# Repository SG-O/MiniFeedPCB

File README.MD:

# Main PCB for automated SMT Feeder #

## Documentation ##

You can find the manufacturing documentation [here.](https://github.com/SG-O/MiniFeedPCB/tree/master/Doc)

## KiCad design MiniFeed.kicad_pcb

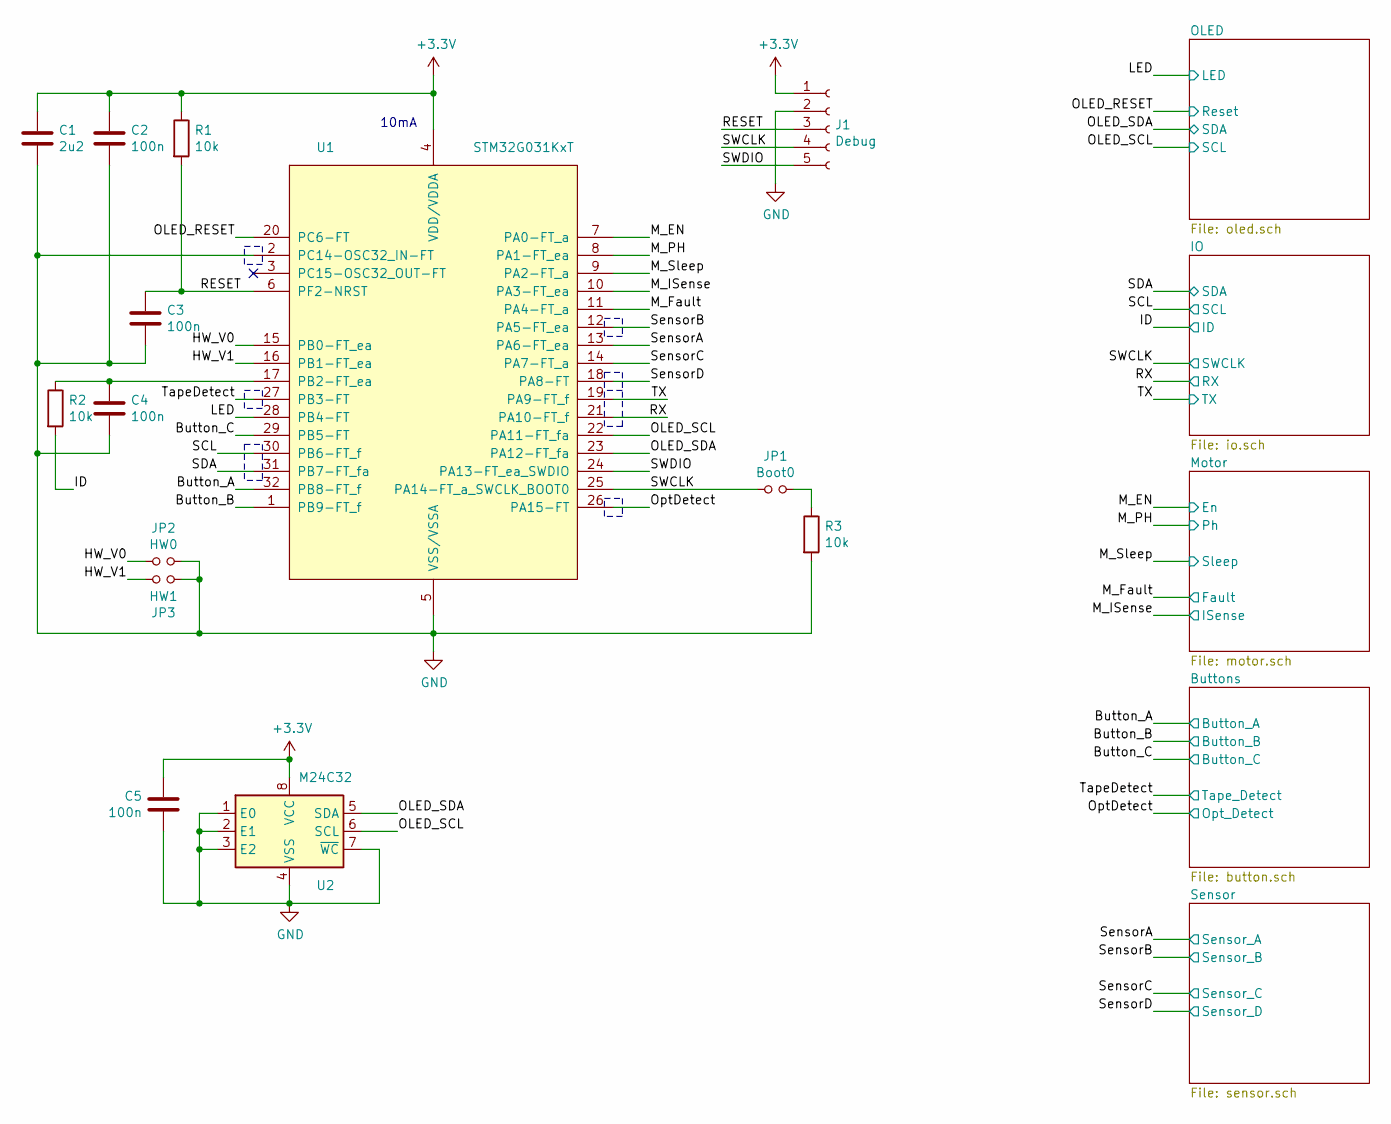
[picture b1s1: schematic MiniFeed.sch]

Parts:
C1: 2u2; C_0805_2012Metric; lcsc# C19110
C2, C3, C4, C5: 100n; C_0603_1608Metric; lcsc# C1591
J1: Debug; PinSocket_1x05_P1.27mm_Vertical
JP1: Boot0; SolderJumper-2_P1.3mm_Open_RoundedPad1.0x1.5mm
JP2: HW0; SolderJumper-2_P1.3mm_Open_RoundedPad1.0x1.5mm
JP3: HW1; SolderJumper-2_P1.3mm_Open_RoundedPad1.0x1.5mm
R1, R2, R3: 10k; R_0603_1608Metric; lcsc# C128781
U1: STM32G031KxT; LQFP-32_7x7mm_P0.8mm; lcsc# C432203
U2: M24C32; SOIC-8_3.9x4.9mm_P1.27mm; lcsc# C7998

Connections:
+3V3: C1.1, C2.1, C5.1, J1.1, R1.1, U1.4 (VDD/VDDA), U2.8 (VCC); also elsewhere on the board
/Button_A: U1.32 (PB8-FT_f); also elsewhere on the board
/Button_B: U1.1 (PB9-FT_f); also elsewhere on the board
/Button_C: U1.29 (PB5-FT); also elsewhere on the board
/HW_V0: JP2.1, U1.15 (PB0-FT_ea)
/HW_V1: JP3.1, U1.16 (PB1-FT_ea)
/ID: R2.2; also elsewhere on the board
/LED: U1.28 (PB4-FT); also elsewhere on the board
/M_EN: U1.7 (PA0-FT_a); also elsewhere on the board
/M_Fault: U1.11 (PA4-FT_a); also elsewhere on the board
/M_ISense: U1.10 (PA3-FT_ea); also elsewhere on the board
/M_PH: U1.8 (PA1-FT_ea); also elsewhere on the board
/M_Sleep: U1.9 (PA2-FT_a); also elsewhere on the board
/OLED_RESET: U1.20 (PC6-FT); also elsewhere on the board
/OLED_SCL: U1.22 (PA11-FT_fa), U2.6 (SCL); also elsewhere on the board
/OLED_SDA: U1.23 (PA12-FT_fa), U2.5 (SDA); also elsewhere on the board
/OptDetect: U1.26 (PA15-FT); also elsewhere on the board
/RESET: C3.1, J1.3, R1.2, U1.6 (PF2-NRST)
/RX: U1.21 (PA10-FT_f); also elsewhere on the board
/SCL: U1.30 (PB6-FT_f); also elsewhere on the board
/SDA: U1.31 (PB7-FT_fa); also elsewhere on the board
/SWCLK: J1.4, JP1.1, U1.25 (PA14-FT_a_SWCLK_BOOT0); also elsewhere on the board
/SWDIO: J1.5, U1.24 (PA13-FT_ea_SWDIO)
/SensorA: U1.13 (PA6-FT_ea); also elsewhere on the board
/SensorB: U1.12 (PA5-FT_ea); also elsewhere on the board
/SensorC: U1.14 (PA7-FT_a); also elsewhere on the board
/SensorD: U1.18 (PA8-FT); also elsewhere on the board
/TX: U1.19 (PA9-FT_f); also elsewhere on the board
/TapeDetect: U1.27 (PB3-FT); also elsewhere on the board
GND: C1.2, C2.2, C3.2, C4.2, C5.2, J1.2, JP2.2, JP3.2, R3.2, U1.2 (PC14-OSC32_IN-FT), U1.5 (VSS/VSSA), U2.1 (E0), U2.2 (E1), U2.3 (E2), U2.4 (VSS), U2.7 (~WC); also elsewhere on the board
unnamed: C4.1, R2.1, U1.17 (PB2-FT_ea)
unnamed: JP1.2, R3.1

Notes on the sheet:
10mA

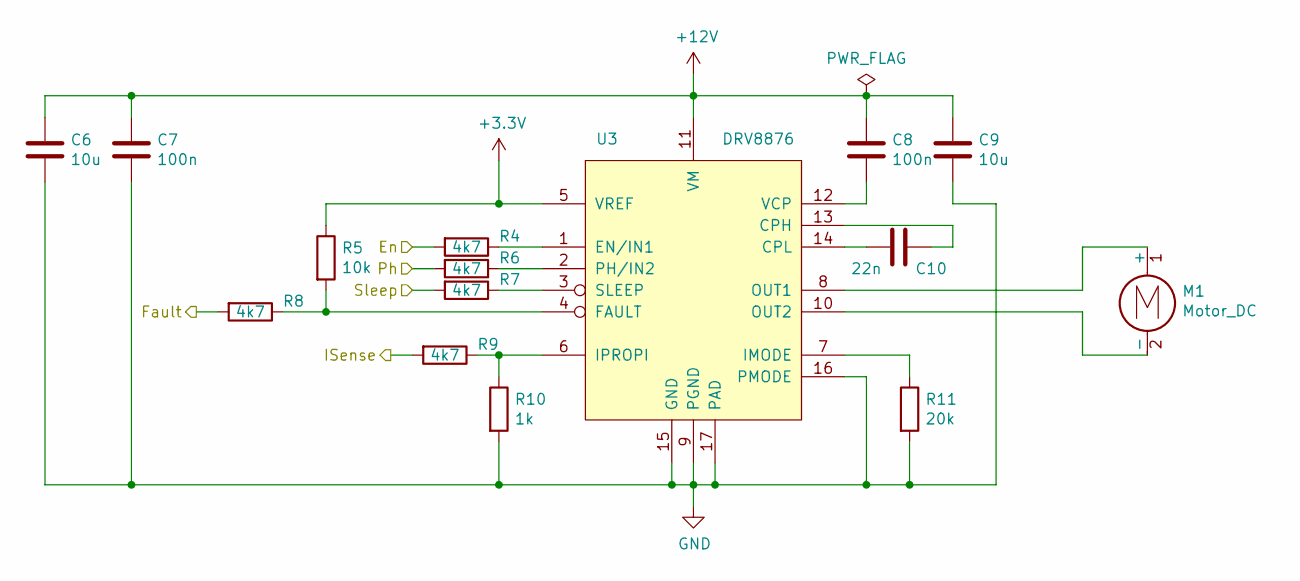
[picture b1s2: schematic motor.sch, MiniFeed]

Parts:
C6, C9: 10u; C_1206_3216Metric; lcsc# C14860
C7, C8: 100n; C_0603_1608Metric; lcsc# C1591
C10: 22n; C_0603_1608Metric; lcsc# C21122
M1: Motor_DC; MotorN20
R4, R6, R7, R8, R9: 4k7; R_0603_1608Metric; lcsc# C304093
R5: 10k; R_0603_1608Metric; lcsc# C128781
R10: 1k; R_0603_1608Metric; lcsc# C165976
R11: 20k; R_0603_1608Metric; lcsc# C135618
U3: DRV8876; HTSSOP-16-1EP_4.4x5mm_P0.65mm_EP3.4x5mm_Mask2.46x2.31mm_The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; lcsc# C575551

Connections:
+3V3: R5.1, U3.5 (VREF); also elsewhere on the board
+12V: C6.1, C7.1, C8.1, C9.1, U3.11 (VM); also elsewhere on the board
/M_EN: R4.2; also elsewhere on the board
/M_Fault: R8.2; also elsewhere on the board
/M_ISense: R9.2; also elsewhere on the board
/M_PH: R6.2; also elsewhere on the board
/M_Sleep: R7.2; also elsewhere on the board
GND: C6.2, C7.2, C9.2, R10.2, R11.2, U3.9 (PGND), U3.15 (GND), U3.16 (PMODE), U3.17 (PAD); also elsewhere on the board
unnamed: C8.2, U3.12 (VCP)
unnamed: C10.1, U3.13 (CPH)
unnamed: C10.2, U3.14 (CPL)
unnamed: M1.1 (+), U3.8 (OUT1)
unnamed: M1.2 (-), U3.10 (OUT2)
unnamed: R4.1, U3.1 (EN/IN1)
unnamed: R5.2, R8.1, U3.4 (FAULT)
unnamed: R6.1, U3.2 (PH/IN2)
unnamed: R7.1, U3.3 (SLEEP)
unnamed: R9.1, R10.1, U3.6 (IPROPI)
unnamed: R11.1, U3.7 (IMODE)

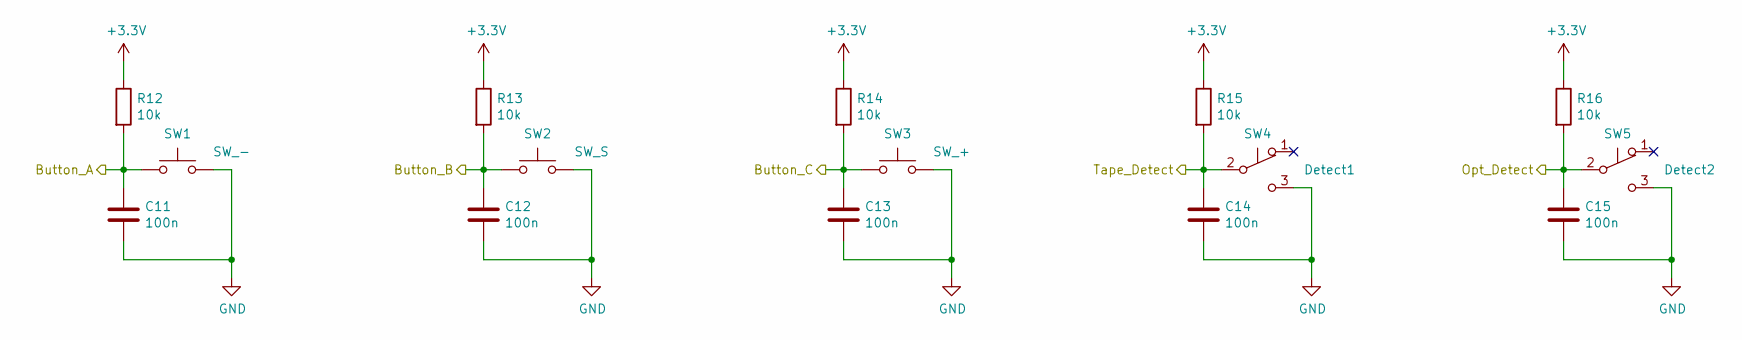
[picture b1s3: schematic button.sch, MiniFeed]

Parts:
C11, C12, C13, C14, C15: 100n; C_0603_1608Metric; lcsc# C1591
R12, R13, R14, R15, R16: 10k; R_0603_1608Metric; lcsc# C128781
SW1: SW_-; SW_SPST_TS-1065A-B3D4; lcsc# C498295
SW2: SW_S; SW_SPST_TS-1065A-B3D4; lcsc# C498295
SW3: SW_+; SW_SPST_TS-1065A-B3D4; lcsc# C498295
SW4: Detect1; MicroSwitchSMDLanding
SW5: Detect2; MicroSwitchSMDLanding

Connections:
+3V3: R12.1, R13.1, R14.1, R15.1, R16.1; also elsewhere on the board
/Button_A: C11.1, R12.2, SW1.1; also elsewhere on the board
/Button_B: C12.1, R13.2, SW2.1; also elsewhere on the board
/Button_C: C13.1, R14.2, SW3.1; also elsewhere on the board
/OptDetect: C15.1, R16.2, SW5.2 (B); also elsewhere on the board
/TapeDetect: C14.1, R15.2, SW4.2 (B); also elsewhere on the board
GND: C11.2, C12.2, C13.2, C14.2, C15.2, SW1.2, SW2.2, SW3.2, SW4.3 (C), SW5.3 (C); also elsewhere on the board

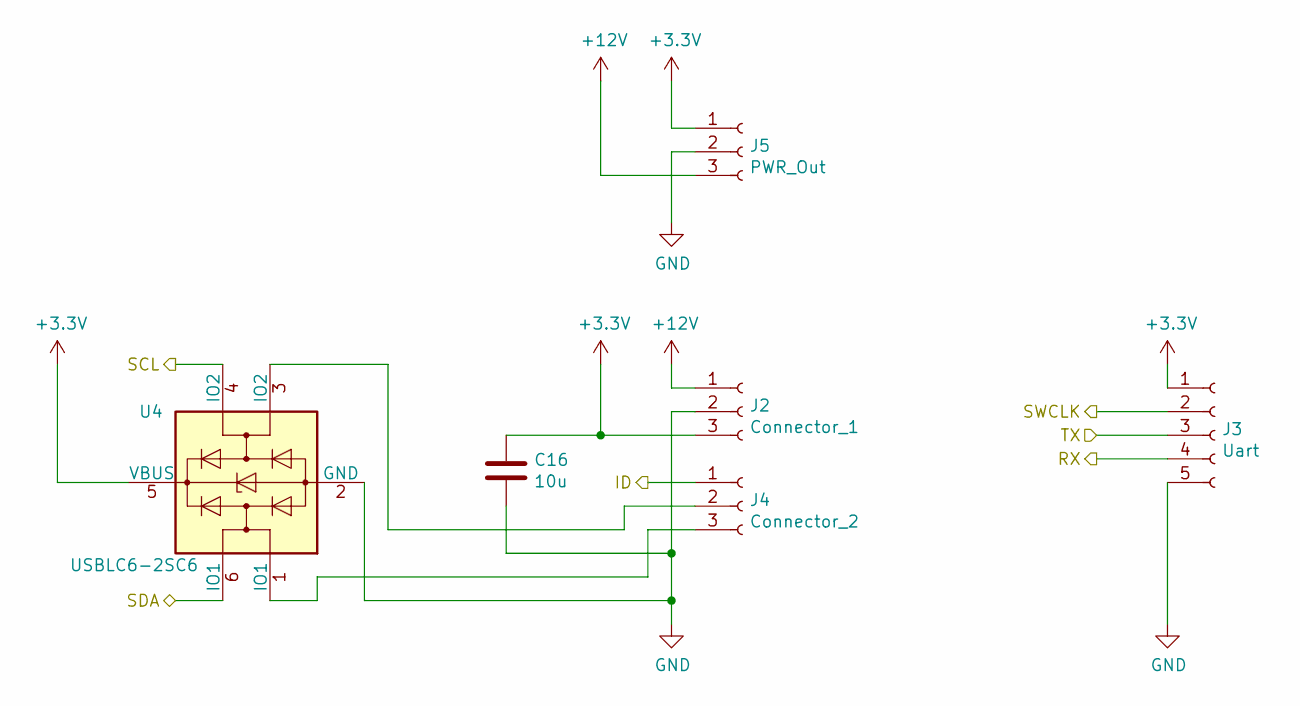
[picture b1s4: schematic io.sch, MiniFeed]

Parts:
C16: 10u; C_1206_3216Metric; lcsc# C14860
J2: Connector_1; PogoTarget_P2.5
J3: Uart; PinSocket_1x05_P2.54mm_Vertical
J4: Connector_2; PogoTarget_P2.5
J5: PWR_Out; PinSocket_1x03_P1.27mm_Vertical_SMD_Pin1Left
U4: USBLC6-2SC6; SOT-23-6; lcsc# C558442

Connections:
+3V3: C16.1, J2.3, J3.1, J5.1, U4.5 (VBUS); also elsewhere on the board
+12V: J2.1, J5.3; also elsewhere on the board
/ID: J4.1; also elsewhere on the board
/RX: J3.4; also elsewhere on the board
/SCL: U4.4 (IO2); also elsewhere on the board
/SDA: U4.6 (IO1); also elsewhere on the board
/SWCLK: J3.2; also elsewhere on the board
/TX: J3.3; also elsewhere on the board
GND: C16.2, J2.2, J3.5, J5.2, U4.2 (GND); also elsewhere on the board
unnamed: J4.2, U4.3 (IO2)
unnamed: J4.3, U4.1 (IO1)

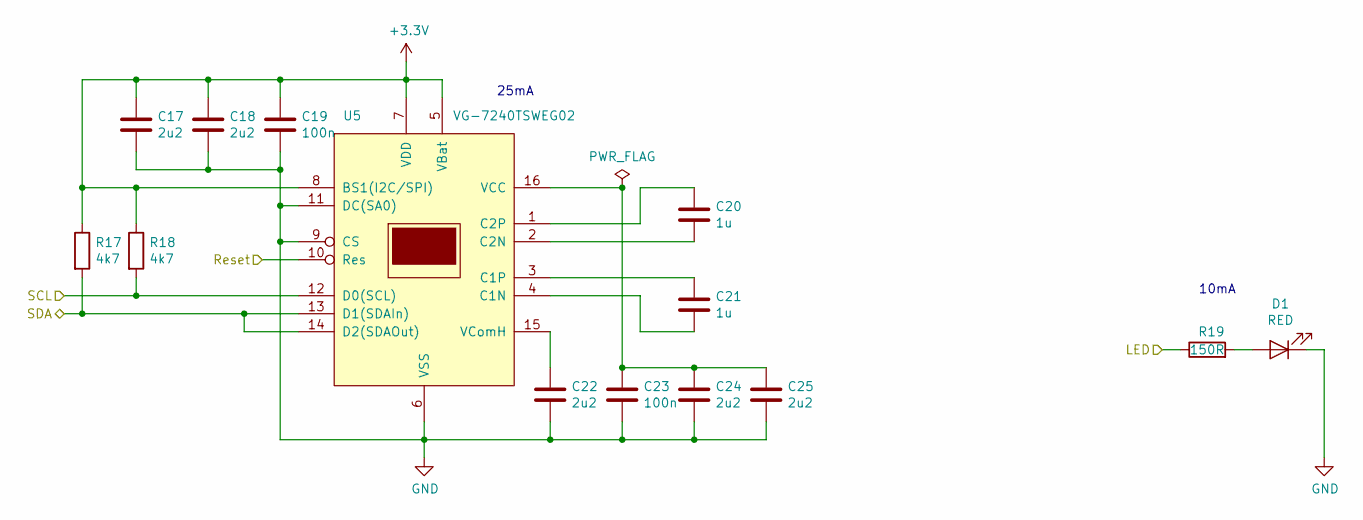
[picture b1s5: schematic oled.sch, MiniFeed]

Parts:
C17, C18, C22, C24, C25: 2u2; C_0805_2012Metric; lcsc# C19110
C19, C23: 100n; C_0603_1608Metric; lcsc# C1591
C20, C21: 1u; C_0603_1608Metric; lcsc# C29936
D1: RED; LED_0603_1608Metric_SIDE; lcsc# C125114
R17, R18: 4k7; R_0603_1608Metric; lcsc# C304093
R19: 150R; R_0603_1608Metric; lcsc# C217745
U5: VG-7240TSWEG02; VG-7240TSWEG02-mirror

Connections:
+3V3: C17.1, C18.1, C19.1, R17.1, R18.1, U5.5 (VBat), U5.7 (VDD), U5.8 (BS1(I2C/SPI)); also elsewhere on the board
/LED: R19.1; also elsewhere on the board
/OLED_RESET: U5.10 (Res); also elsewhere on the board
/OLED_SCL: R18.2, U5.12 (D0(SCL)); also elsewhere on the board
/OLED_SDA: R17.2, U5.13 (D1(SDAIn)), U5.14 (D2(SDAOut)); also elsewhere on the board
GND: C17.2, C18.2, C19.2, C22.2, C23.2, C24.2, C25.2, D1.1 (K), U5.6 (VSS), U5.9 (CS), U5.11 (DC(SA0)); also elsewhere on the board
unnamed: C20.1, U5.1 (C2P)
unnamed: C20.2, U5.2 (C2N)
unnamed: C21.1, U5.3 (C1P)
unnamed: C21.2, U5.4 (C1N)
unnamed: C22.1, U5.15 (VComH)
unnamed: C23.1, C24.1, C25.1, U5.16 (VCC)
unnamed: D1.2 (A), R19.2

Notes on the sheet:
25mA
10mA

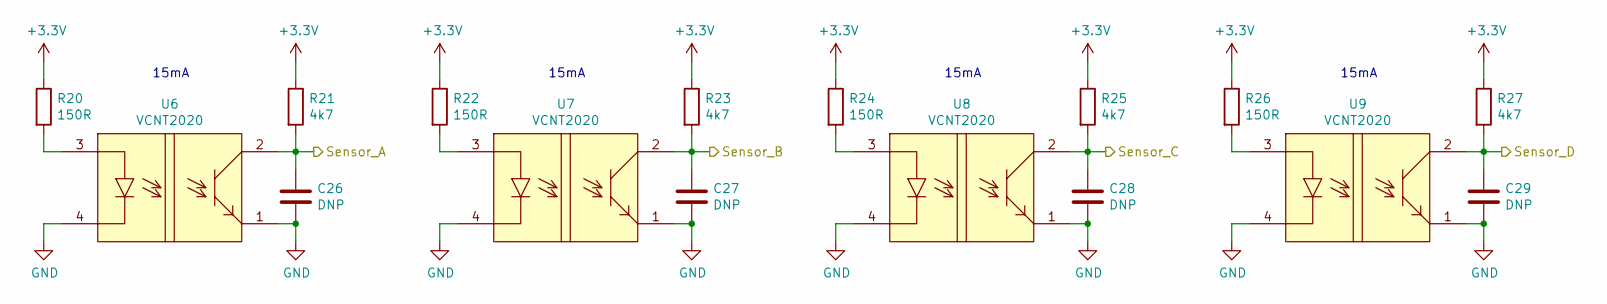
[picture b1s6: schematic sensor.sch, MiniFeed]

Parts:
C26, C27, C28, C29: DNP; C_0603_1608Metric
R20, R22, R24, R26: 150R; R_0603_1608Metric; lcsc# C217745
R21, R23, R25, R27: 4k7; R_0603_1608Metric; lcsc# C304093
U6, U7, U8, U9: VCNT2020; vcnt2020

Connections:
+3V3: R20.1, R21.1, R22.1, R23.1, R24.1, R25.1, R26.1, R27.1; also elsewhere on the board
/SensorA: C26.1, R21.2, U6.2; also elsewhere on the board
/SensorB: C27.1, R23.2, U7.2; also elsewhere on the board
/SensorC: C28.1, R25.2, U8.2; also elsewhere on the board
/SensorD: C29.1, R27.2, U9.2; also elsewhere on the board
GND: C26.2, C27.2, C28.2, C29.2, U6.1, U6.4, U7.1, U7.4, U8.1, U8.4, U9.1, U9.4; also elsewhere on the board
unnamed: R20.2, U6.3
unnamed: R22.2, U7.3
unnamed: R24.2, U8.3
unnamed: R26.2, U9.3

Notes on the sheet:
15mA

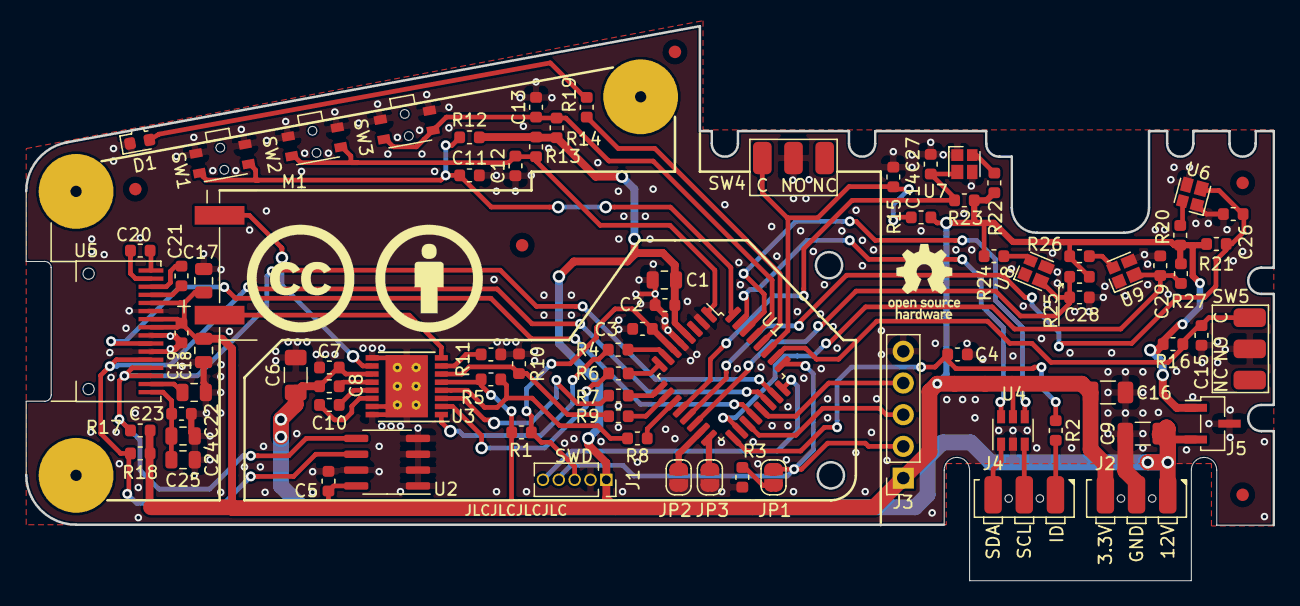
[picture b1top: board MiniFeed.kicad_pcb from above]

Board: 2 copper layers, 100.0 x 44.4 mm, 92 parts (1 on the bottom side), 57 nets.

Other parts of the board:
Fid1, Fid2, Fid3, Fid4, Fid5: Fiducial_1mm_Mask2mm
G1: CC
G2: BY
G3: OSHW-Logo_5.7x6mm_SilkScreen
G4: SG-O; Logo_SG-O
Mech1, Mech2, Mech3: SolderStandoffM3x5

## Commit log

2020-11-15 Added image to readme
2020-12-17 Fixed LDO design: Added resistor to increase ESR for LDO. Added diode to LDO to protect the regulator if the input instantaneously is shorted to GND.
    Fixed the SCL trace.
2020-12-17 Made BOM beautiful and searchable
2021-01-06 Updated CAD model
2021-01-31 Removed voltage regulator Added input protection Added more VCNT2020 sensors Fixed the motor driver overcurrent protection Replaced push buttons with smaller models
2021-01-31 Updated PCB design
2021-02-01 Moved C24 reference to resolve silkscreen collision
2021-02-01 Changed 0.33mm vias to 0.3mm
2021-02-24 Added an optional power output header Changed the resistors for the VCNT2020 to improve performance

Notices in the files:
MiniFeed.kicad_pcb:
©CC BY 4.0
